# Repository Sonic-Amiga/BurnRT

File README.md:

# BurnRT fuse ROM programmer

 This is a programmer for old OTP fuse PROM chips. Developed and tested with russian
556РТ (556RT) series, however should also be able to work with Western analogs.

 The project has been restored from old P-CAD sources, shared on the original project
forum (https://zx-pk.ru/threads/15617-programmator-ppzu-155re3-556rt4-i-drugikh ;
russian language).

Current versions:

* Hardware v2.3
* Software v2.0
* Firmware v1.1
* Case v1.0

Unfortunately at the moment only a binary version of the software for Windows OS is available.

# Supported chips

155РЕ3 (155RE3), western analogs SN74188N, N8223N
556РТ4 (556RT4), western analog 82S126
556РТ11 (556RT11), western analog 82S129
556РТ5 (556RT5), western analog IP3604
556РТ17 (556RT17), western analog IP3624A
556РТ6 (556RT6)
556РТ7 (556RT7)
556РТ12, western analog N82S136
556РТ13, western analog N82S137
556РТ14 (556RT14)
556РТ15 (556RT15)

# Distribution

There was originally no clear license terms defined. I asked at least one of original authors
of the schematic; he was not against me opensourcing the design. I am not a fan of this legal
stuff; let's consider it public domain. Any improvements are welcome; i will gladly accept them
into the repository.

3D printed case design is licensed under Creative Commons license: https://www.thingiverse.com/thing:2911557

# Contacts

Please direct all questions to pavel_fedin@mail.ru or to the aforementioned forum.

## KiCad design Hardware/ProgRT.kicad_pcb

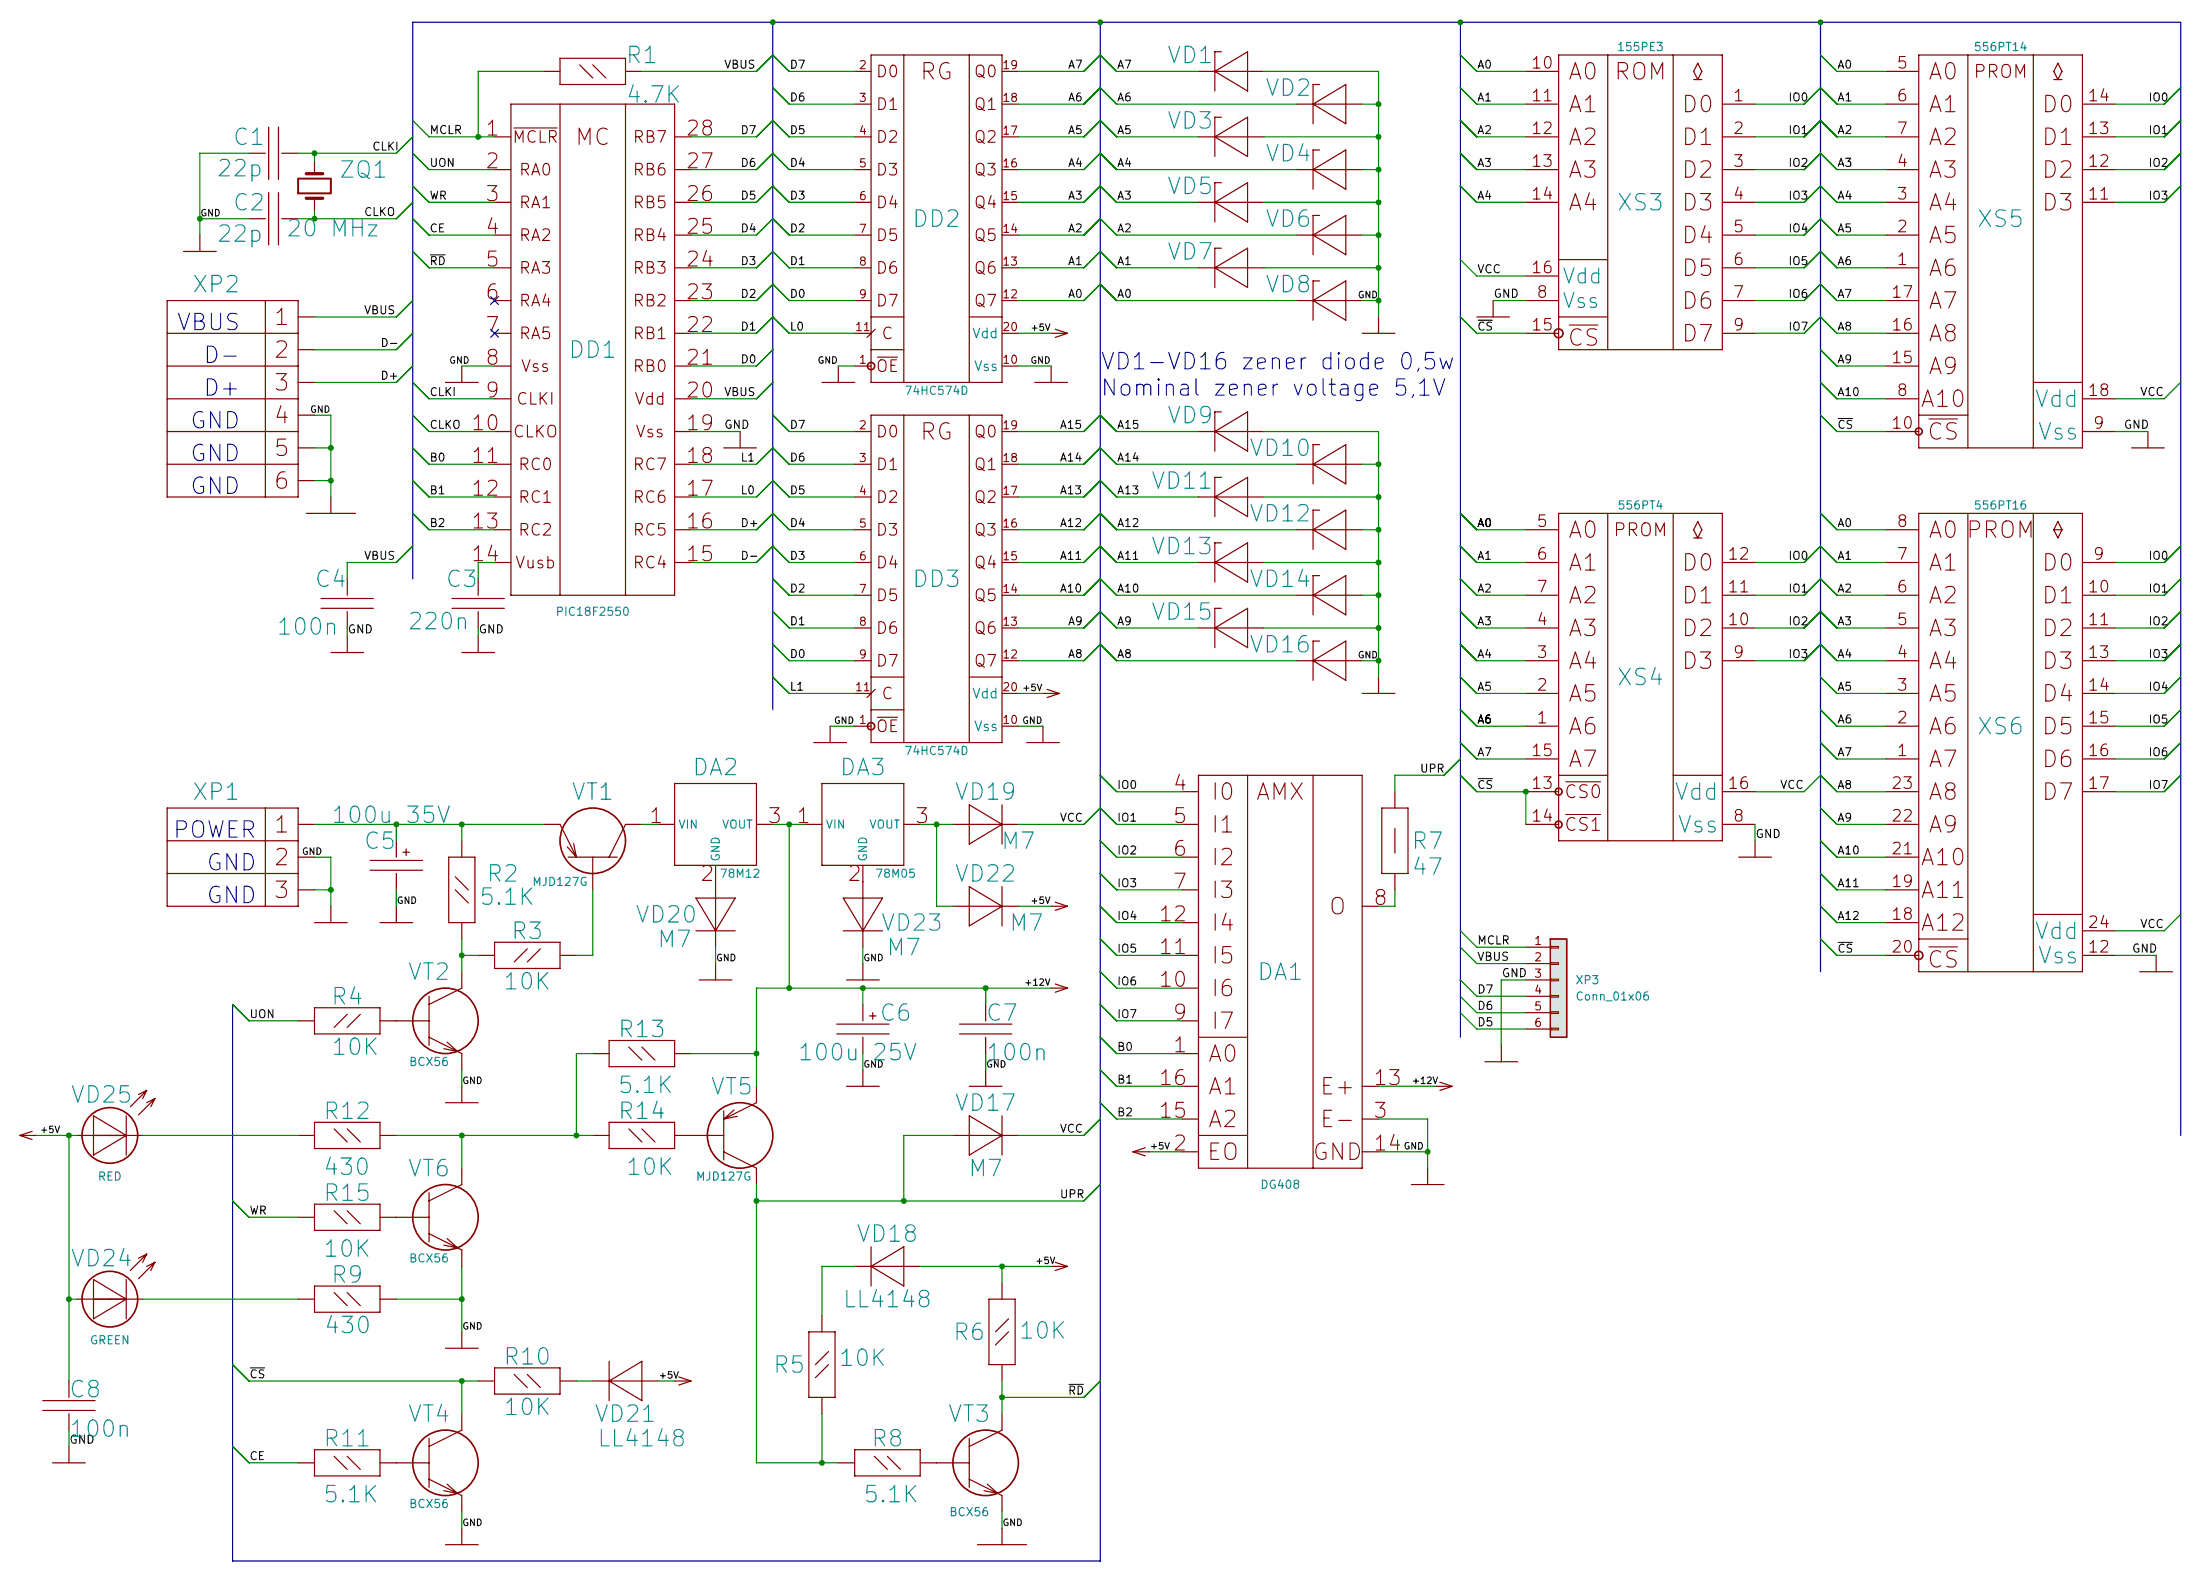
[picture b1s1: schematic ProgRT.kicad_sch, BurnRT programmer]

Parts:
C1, C2: 22p; C_0805_2012Metric_Pad1.18x1.45mm_HandSolder
C3: 220n; C_0805_2012Metric_Pad1.18x1.45mm_HandSolder
C4, C7: 100n; C_0805_2012Metric_Pad1.18x1.45mm_HandSolder
C5: 100u 35V; CP_Radial_D8.0mm_P3.80mm
C6: 100u 25V; CP_Radial_D8.0mm_P3.80mm
C8: 100n; C_1206_3216Metric_Pad1.33x1.80mm_HandSolder
DA1: DG408; SOIC-16_3.9x9.9mm_P1.27mm
DA2: 78M12; TO-252-2
DA3: 78M05; TO-252-2
DD1: PIC18F2550; SOIC-28W_7.5x18.7mm_P1.27mm
DD2, DD3: 74HC574D; SOIC-20W_7.5x12.8mm_P1.27mm
R1: 4.7K; R_0805_2012Metric_Pad1.20x1.40mm_HandSolder
R2, R8, R11, R13: 5.1K; R_0805_2012Metric_Pad1.20x1.40mm_HandSolder
R3: R_0805_2012Metric_Pad1.20x1.40mm_HandSolder
R4, R5, R6, R10, R14, R15: 10K; R_0805_2012Metric_Pad1.20x1.40mm_HandSolder
R7: 47; R_2512_6332Metric_Pad1.40x3.35mm_HandSolder
R9, R12: 430; R_0805_2012Metric_Pad1.20x1.40mm_HandSolder
VD1, VD2, VD3, VD4, VD5, VD6, VD7, VD8, VD9, VD10, VD11, VD12, VD13, VD14, VD15, VD16: BZV55-C5V1; D_MiniMELF
VD17, VD19, VD20, VD22: M7; D_SMA
VD18, VD21: LL4148; D_SMA
VD23: D_SMA
VD24: GREEN; LED_1206_3216Metric_Pad1.42x1.75mm_HandSolder
VD25: RED; LED_1206_3216Metric_Pad1.42x1.75mm_HandSolder
VT1, VT5: MJD127G; TO-252-2
VT2, VT3, VT4, VT6: BCX56; SOT-89-3
XP1: DC-005_1; BarrelJack_GCT_DCJ200-10-A_Horizontal
XP2: USB_TYPE_B_1; USB_Mini-B_Lumberg_2486_01_Horizontal
XP3: Conn_01x06; PinHeader_1x06_P2.54mm_Vertical
XS3: 155РЕ3; DIP_Socket-16_W4.3_W5.08_W7.62_W10.16_W10.9_3M_216-3340-00-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
XS4: 556РT4; DIP_Socket-16_W4.3_W5.08_W7.62_W10.16_W10.9_3M_216-3340-00-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
XS5: 556РТ14; DIP_Socket-18_W4.3_W5.08_W7.62_W10.16_W10.9_3M_218-3341-00-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
XS6: 556РТ16; DIP_Socket-24_W11.9_W12.7_W15.24_W17.78_W18.5_3M_224-1275-0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
ZQ1: 20 MHz; Crystal_HC49-U_Vertical

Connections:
/A0: DD2.12 (Q7), VD8.1 (C), XS3.10 (A0), XS4.5 (A0), XS5.5 (A0), XS6.8 (A0)
/A1: DD2.13 (Q6), VD7.1 (C), XS3.11 (A1), XS4.6 (A1), XS5.6 (A1), XS6.7 (A1)
/A2: DD2.14 (Q5), VD6.1 (C), XS3.12 (A2), XS4.7 (A2), XS5.7 (A2), XS6.6 (A2)
/A3: DD2.15 (Q4), VD5.1 (C), XS3.13 (A3), XS4.4 (A3), XS5.4 (A3), XS6.5 (A3)
/A4: DD2.16 (Q3), VD4.1 (C), XS3.14 (A4), XS4.3 (A4), XS5.3 (A4), XS6.4 (A4)
/A5: DD2.17 (Q2), VD3.1 (C), XS4.2 (A5), XS5.2 (A5), XS6.3 (A5)
/A6: DD2.18 (Q1), VD2.1 (C), XS4.1 (A6), XS5.1 (A6), XS6.2 (A6)
/A7: DD2.19 (Q0), VD1.1 (C), XS4.15 (A7), XS5.17 (A7), XS6.1 (A7)
/A8: DD3.12 (Q7), VD16.1 (C), XS5.16 (A8), XS6.23 (A8)
/A9: DD3.13 (Q6), VD15.1 (C), XS5.15 (A9), XS6.22 (A9)
/A10: DD3.14 (Q5), VD14.1 (C), XS5.8 (A10), XS6.21 (A10)
/A11: DD3.15 (Q4), VD13.1 (C), XS6.19 (A11)
/A12: DD3.16 (Q3), VD12.1 (C), XS6.18 (A12)
/A13: DD3.17 (Q2), VD11.1 (C)
/A14: DD3.18 (Q1), VD10.1 (C)
/A15: DD3.19 (Q0), VD9.1 (C)
/B0: DA1.1 (A0), DD1.11 (RC0)
/B1: DA1.16 (A1), DD1.12 (RC1)
/B2: DA1.15 (A2), DD1.13 (RC2)
/CE: DD1.4 (RA2), R11.1
/CLKI: C1.1 (2), DD1.9 (CLKI), ZQ1.2
/CLKO: C2.1 (2), DD1.10 (CLKO), ZQ1.1
/D0: DD1.21 (RB0), DD2.9 (D7), DD3.9 (D7)
/D1: DD1.22 (RB1), DD2.8 (D6), DD3.8 (D6)
/D2: DD1.23 (RB2), DD2.7 (D5), DD3.7 (D5)
/D3: DD1.24 (RB3), DD2.6 (D4), DD3.6 (D4)
/D4: DD1.25 (RB4), DD2.5 (D3), DD3.5 (D3)
/D5: DD1.26 (RB5), DD2.4 (D2), DD3.4 (D2), XP3.6
/D6: DD1.27 (RB6), DD2.3 (D1), DD3.3 (D1), XP3.5
/D7: DD1.28 (RB7), DD2.2 (D0), DD3.2 (D0), XP3.4
/D+: DD1.16 (RC5), XP2.3 (D+)
/D-: DD1.15 (RC4), XP2.2 (D-)
/GND: C1.2 (1), C2.2 (1), C3.2 (1), C4.2 (1), C5.2, C6.2, C7.1 (2), C8.1 (2), DA1.3 (E-), DA1.14 (GND), DD1.8 (VSS@1), DD1.19 (VSS@2), DD2.1 (!OE), DD2.10 (Vss), DD3.1 (!OE), DD3.10 (Vss), R9.1, VD1.2 (A), VD2.2 (A), VD3.2 (A), VD4.2 (A), VD5.2 (A), VD6.2 (A), VD7.2 (A), VD8.2 (A), VD9.2 (A), VD10.2 (A), VD11.2 (A), VD12.2 (A), VD13.2 (A), VD14.2 (A), VD15.2 (A), VD16.2 (A), VD20.1 (C), VD23.1 (C), VT2.3 (E), VT3.3 (E), VT4.3 (E), VT6.3 (E), XP1.2, XP1.3, XP2.4 (GND@2), XP2.5 (GND@1), XP2.6 (GND@3), XP3.3, XS3.8 (Vss), XS4.8 (Vss), XS5.9 (Vss), XS6.12 (Vss)
/IO0: DA1.4 (I0), XS3.1 (D0), XS4.12 (D0), XS5.14 (D0), XS6.9 (D0)
/IO1: DA1.5 (I1), XS3.2 (D1), XS4.11 (D1), XS5.13 (D1), XS6.10 (D1)
/IO2: DA1.6 (I2), XS3.3 (D2), XS4.10 (D2), XS5.12 (D2), XS6.11 (D2)
/IO3: DA1.7 (I3), XS3.4 (D3), XS4.9 (D3), XS5.11 (D3), XS6.13 (D3)
/IO4: DA1.12 (I4), XS3.5 (D4), XS6.14 (D4)
/IO5: DA1.11 (I5), XS3.6 (D5), XS6.15 (D5)
/IO6: DA1.10 (I6), XS3.7 (D6), XS6.16 (D6)
/IO7: DA1.9 (I7), XS3.9 (D7), XS6.17 (D7)
/L0: DD1.17 (RC6), DD2.11 (C)
/L1: DD1.18 (RC7), DD3.11 (C)
/MCLR: DD1.1 (!MCLR), R1.1, XP3.1
/UON: DD1.2 (RA0), R4.1
/UPR: R5.1, R7.1, R8.1, VD17.2 (A), VT5.2 (C)
/VBUS: C4.1 (2), DD1.20 (VDD), R1.2, XP2.1 (VBUS), XP3.2
/VCC: VD17.1 (C), VD19.1 (C), XS3.16 (Vdd), XS4.16 (Vdd), XS5.18 (Vdd), XS6.24 (Vdd)
/WR: DD1.3 (RA1), R15.1
/~CS: R10.1, VT4.2 (C), XS3.15 (!CS), XS4.13 (~CS0), XS4.14 (~CS1), XS5.10 (!CS), XS6.20 (~CS)
/~RD: DD1.5 (RA3), R6.1, VT3.2 (C)
unnamed: C3.1 (2), DD1.14 (VUSB)
unnamed: C5.1, R2.2, VT1.3 (E), XP1.1
unnamed: DA1.8 (O), R7.2
unnamed: DA2.1 (VIN), VT1.2 (C)
unnamed: DA2.2 (GND), VD20.2 (A)
unnamed: DA3.2 (GND), VD23.2 (A)
unnamed: DA3.3 (VOUT), VD19.2 (A), VD22.2 (A)
unnamed: R2.1, R3.1, VT2.2 (C)
unnamed: R3.2, VT1.1 (B)
unnamed: R4.2, VT2.1 (B)
unnamed: R5.2, VD18.1 (C)
unnamed: R8.2, VT3.1 (B)
unnamed: R9.2, VD24.1 (C)
unnamed: R10.2, VD21.1 (C)
unnamed: R11.2, VT4.1 (B)
unnamed: R12.1, VD25.1 (C)
unnamed: R12.2, R13.1, R14.1, VT6.2 (C)
unnamed: R14.2, VT5.1 (B)
unnamed: R15.2, VT6.1 (B)

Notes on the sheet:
GND
VBUS
POWER
VD1-VD16 zener diode 0,5w Nominal zener voltage 5,1V

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
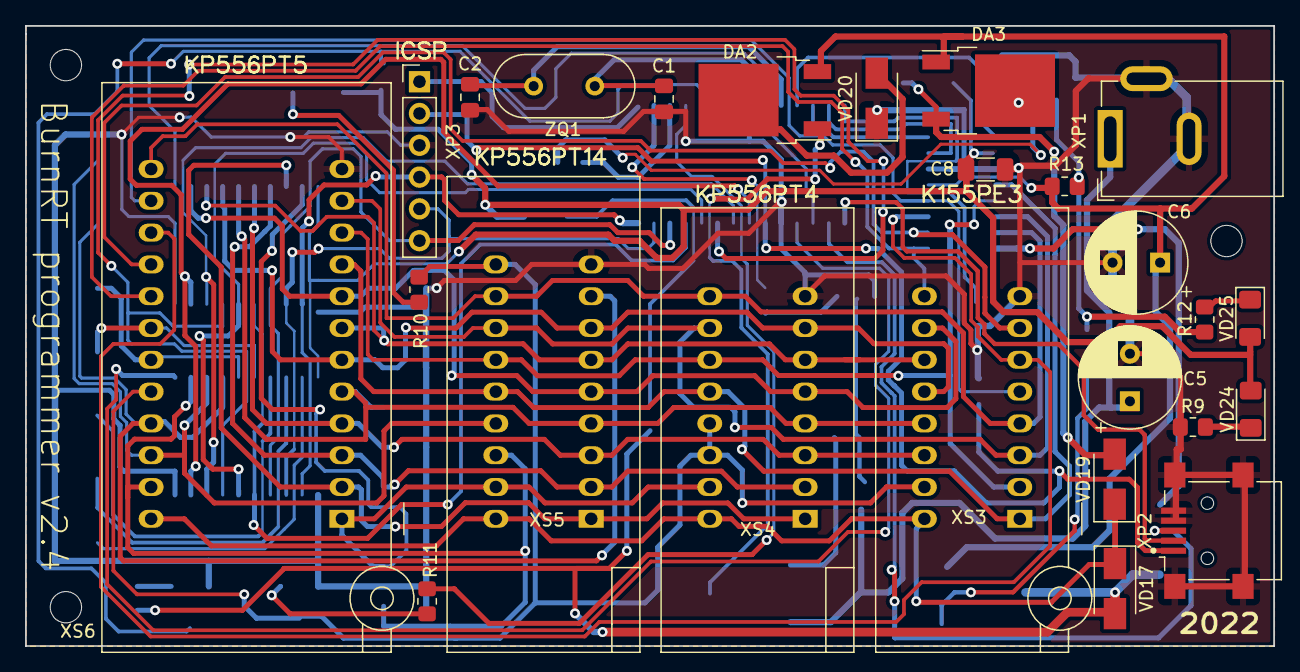
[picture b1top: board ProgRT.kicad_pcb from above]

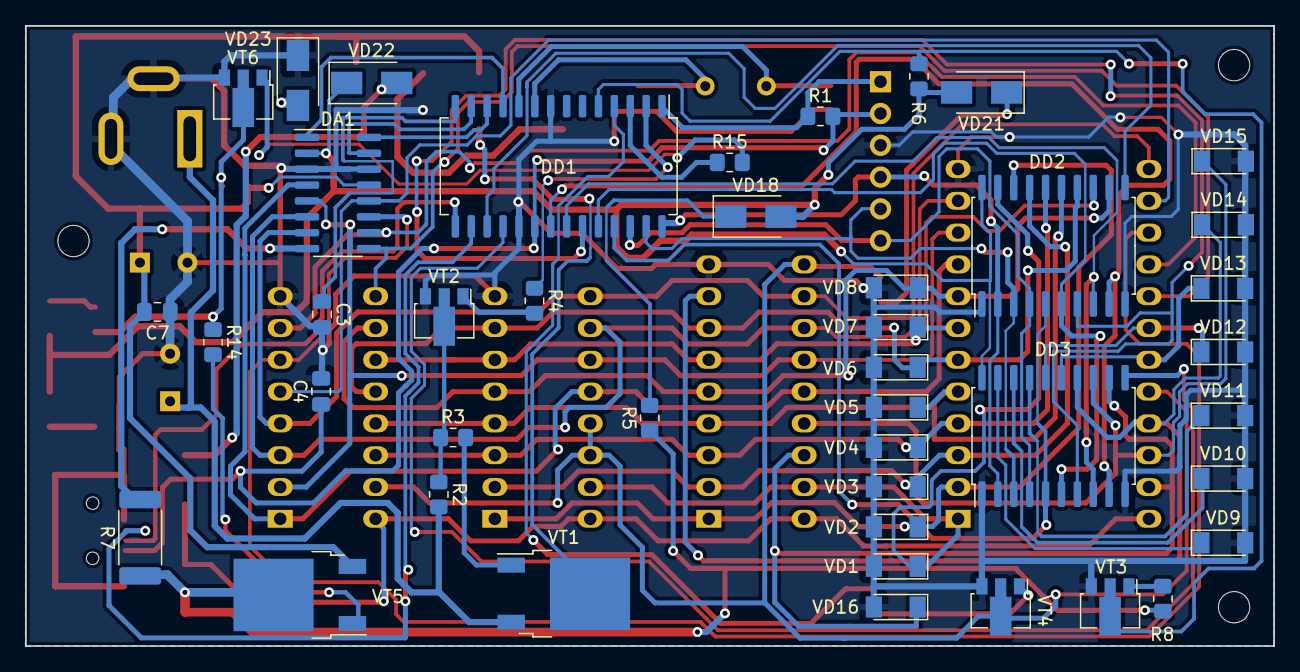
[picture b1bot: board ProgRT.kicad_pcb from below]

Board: 2 copper layers, 99.7 x 49.5 mm, 68 parts (43 on the bottom side), 72 nets.

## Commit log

2022-11-18 Initial import
    The latest schematic, imported from ancient P-CAD format and meticulously
    restored by hands
2022-11-18 PCB from the original single-board layout
    Recovered the PCB from schematic and old gerbers. The gerbers didn't contain
    recent fixups, these parts need to be placed
2022-11-20 Add missing parts
    ICSP connector and C8 capacitor
2022-11-20 Routing complete
    All the parts placed and connected
2022-11-20 Fix DRC errors
    DRC now (almost) passes. Only ZIF socket courtyard overlaps remain, i can't do
    anything about them, at least for now
2022-11-20 Add mounting holes
    Replace drawing with proper mounting hole definitions
2022-11-29 Some PCB optimizations
    Removed some vias, rerouted some tracks, added ground plane
2022-11-29 Small footprint corrections
    - use SMF footprint for Zener diodes, easier to hand-solder
    - use larger footprint for polar caps, extends availability
    - use 3216 LEDs, easier available and easier to hand-solder
2022-11-30 Use MiniMELF Zeners
    Change Zener diodes package again to MiniMELF. Should be easier to hand-solder.
2022-12-17 Fix diodes on silk screen
    Diodes were reversed because pin numbers got corrupted during import. Fix them,
    so that silk screen and fab layer is displayed correctly
2022-12-23 Some fixups
    - Finally remove the missing "empty" frame file
    - Bring back diode types after pins fixup
2022-12-23 Reorganize project
    Move hardware design to a subfolder and provide the current software.
    Unfortunately only binaries are available at the moment
2022-12-28 Add 3D printed case design
    Case design by EvRU from ThingVerse. Let's have all the parts together
